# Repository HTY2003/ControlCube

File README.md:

# ControlCube
A cube of keyboard switches.
It was very bad.
It's taken apart now.
But this is a log :D

This repo includes:
* Rhino3D Design Files for the case and keycaps
* STL exports of the design files for easy viewing
* EAGLE design files for the controller board, switchplate, and switchboard
* Gerber exports of the design files for easy viewing

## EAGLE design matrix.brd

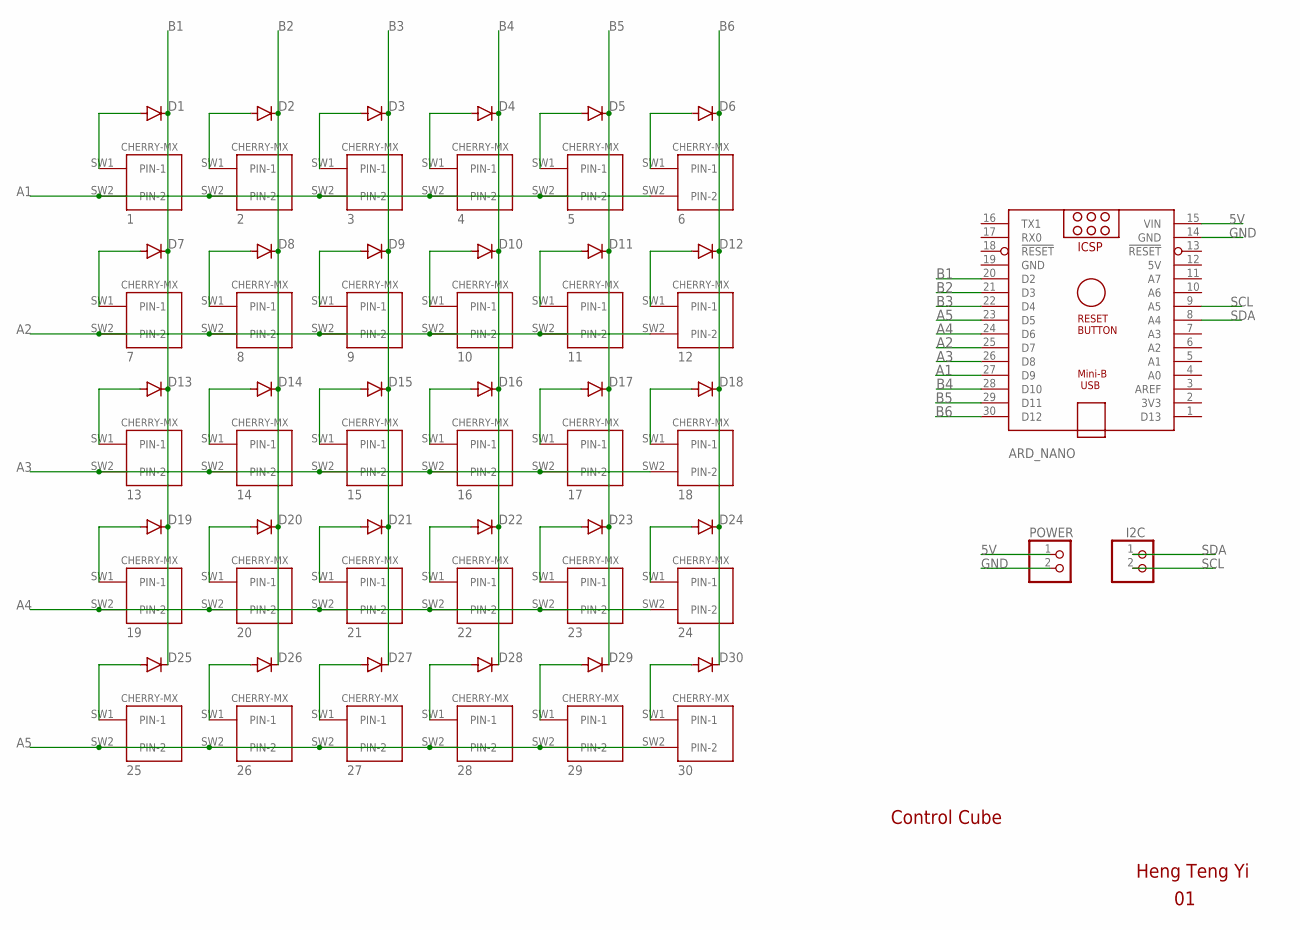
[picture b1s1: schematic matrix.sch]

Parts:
1, 2, 3, 4, 5, 6, 7, 8, 9, 10, 11, 12, 13, 14, 15, 16, 17, 18, 19, 20, 21, 22, 23, 24, 25, 26, 27, 28, 29, 30: CHERRY-MX
ARD_NANO: ARDUINO_NANO
D1, D2, D3, D4, D5, D6, D7, D8, D9, D10, D11, D12, D13, D14, D15, D16, D17, D18, D19, D20, D21, D22, D23, D24, D25, D26, D27, D28, D29, D30: 1N4148DO35-7; DO35-7
I2C: PINHD-1X2/90; 1X02/90
POWER: PINHD-1X2/90; 1X02/90

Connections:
5V: ARD_NANO.12 (5V), ARD_NANO.15 (VIN), POWER.1
A1: 1.SW2 (PIN-2), 2.SW2 (PIN-2), 3.SW2 (PIN-2), 4.SW2 (PIN-2), 5.SW2 (PIN-2), 6.SW2 (PIN-2), ARD_NANO.27 (D9)
A2: 7.SW2 (PIN-2), 8.SW2 (PIN-2), 9.SW2 (PIN-2), 10.SW2 (PIN-2), 11.SW2 (PIN-2), 12.SW2 (PIN-2), ARD_NANO.25 (D7)
A3: 13.SW2 (PIN-2), 14.SW2 (PIN-2), 15.SW2 (PIN-2), 16.SW2 (PIN-2), 17.SW2 (PIN-2), 18.SW2 (PIN-2), ARD_NANO.26 (D8)
A4: 19.SW2 (PIN-2), 20.SW2 (PIN-2), 21.SW2 (PIN-2), 22.SW2 (PIN-2), 23.SW2 (PIN-2), 24.SW2 (PIN-2), ARD_NANO.24 (D6)
A5: 25.SW2 (PIN-2), 26.SW2 (PIN-2), 27.SW2 (PIN-2), 28.SW2 (PIN-2), 29.SW2 (PIN-2), 30.SW2 (PIN-2), ARD_NANO.23 (D5)
B1: ARD_NANO.20 (D2), D1.C, D7.C, D13.C, D19.C, D25.C
B2: ARD_NANO.21 (D3), D2.C, D8.C, D14.C, D20.C, D26.C
B3: ARD_NANO.22 (D4), D3.C, D9.C, D15.C, D21.C, D27.C
B4: ARD_NANO.28 (D10), D4.C, D10.C, D16.C, D22.C, D28.C
B5: ARD_NANO.29 (D11), D5.C, D11.C, D17.C, D23.C, D29.C
B6: ARD_NANO.30 (D12), D6.C, D12.C, D18.C, D24.C, D30.C
GND: ARD_NANO.14 (GND), ARD_NANO.19 (GND), POWER.2
unnamed: 1.SW1 (PIN-1), D1.A
unnamed: 2.SW1 (PIN-1), D2.A
unnamed: 3.SW1 (PIN-1), D3.A
unnamed: 4.SW1 (PIN-1), D4.A
unnamed: 5.SW1 (PIN-1), D5.A
unnamed: 6.SW1 (PIN-1), D6.A
unnamed: 7.SW1 (PIN-1), D7.A
unnamed: 8.SW1 (PIN-1), D8.A
unnamed: 9.SW1 (PIN-1), D9.A
unnamed: 10.SW1 (PIN-1), D10.A
unnamed: 11.SW1 (PIN-1), D11.A
unnamed: 12.SW1 (PIN-1), D12.A
unnamed: 13.SW1 (PIN-1), D13.A
unnamed: 14.SW1 (PIN-1), D14.A
unnamed: 15.SW1 (PIN-1), D15.A
unnamed: 16.SW1 (PIN-1), D16.A
unnamed: 17.SW1 (PIN-1), D17.A
unnamed: 18.SW1 (PIN-1), D18.A
unnamed: 19.SW1 (PIN-1), D19.A
unnamed: 20.SW1 (PIN-1), D20.A
unnamed: 21.SW1 (PIN-1), D21.A
unnamed: 22.SW1 (PIN-1), D22.A
unnamed: 23.SW1 (PIN-1), D23.A
unnamed: 24.SW1 (PIN-1), D24.A
unnamed: 30.SW1 (PIN-1), D30.A
unnamed: 29.SW1 (PIN-1), D29.A
unnamed: 28.SW1 (PIN-1), D28.A
unnamed: 27.SW1 (PIN-1), D27.A
unnamed: 25.SW1 (PIN-1), D25.A
unnamed: 26.SW1 (PIN-1), D26.A
SCL: ARD_NANO.9 (A5), I2C.2
SDA: ARD_NANO.8 (A4), I2C.1

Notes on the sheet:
Heng Teng Yi
Control Cube

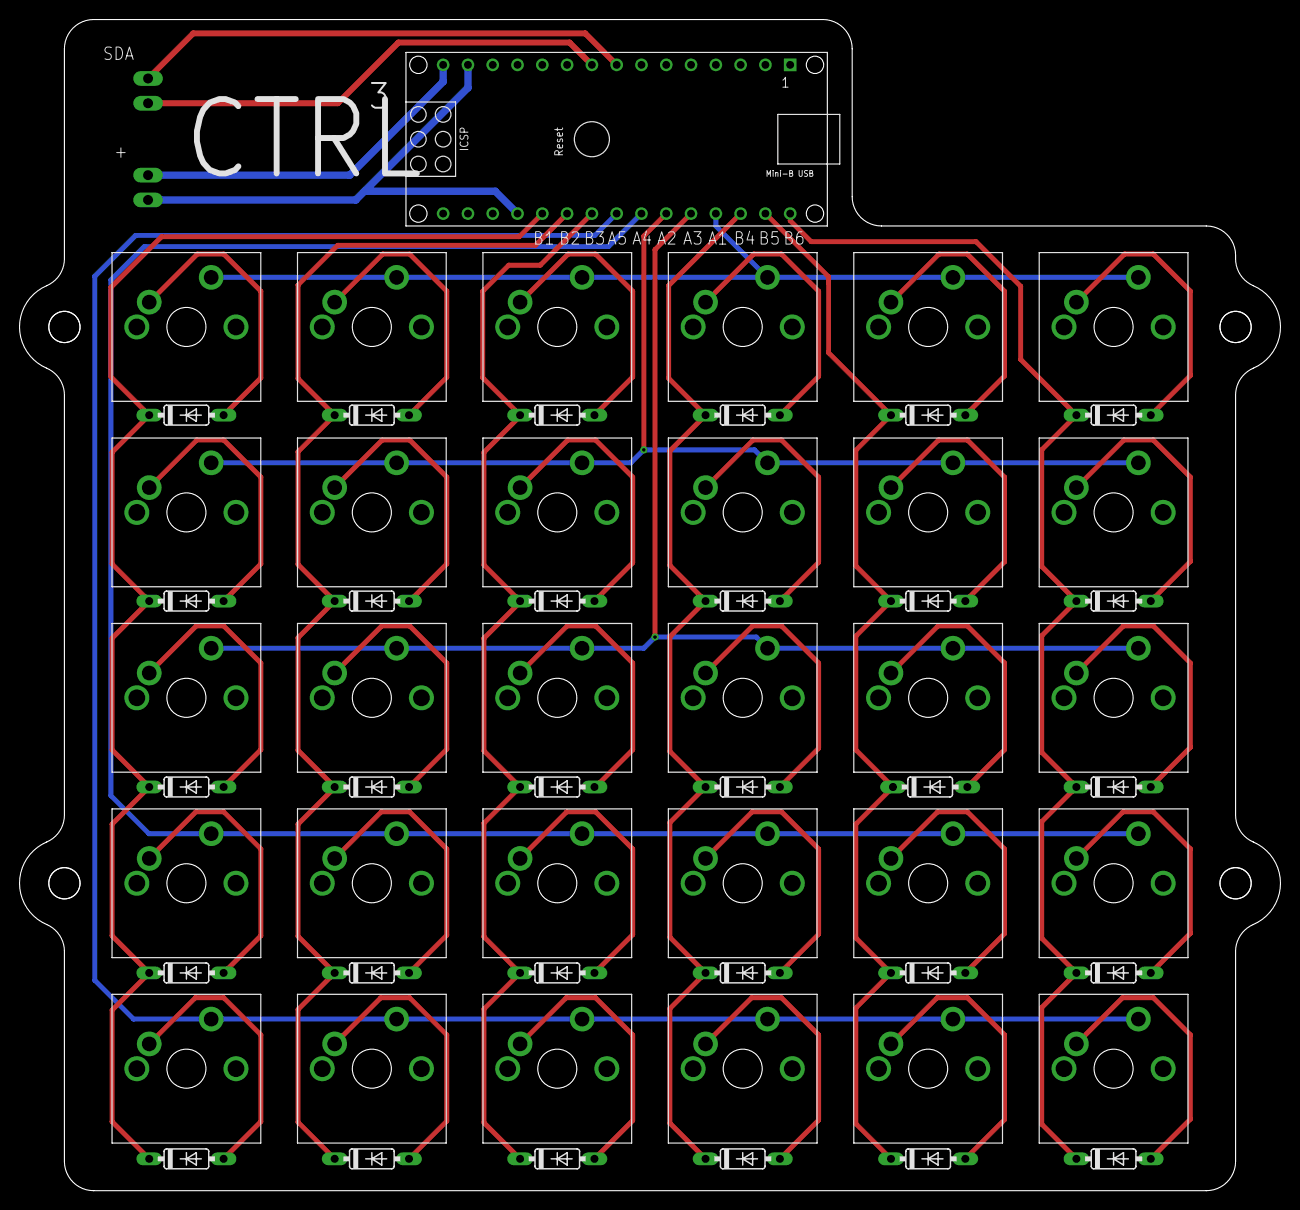
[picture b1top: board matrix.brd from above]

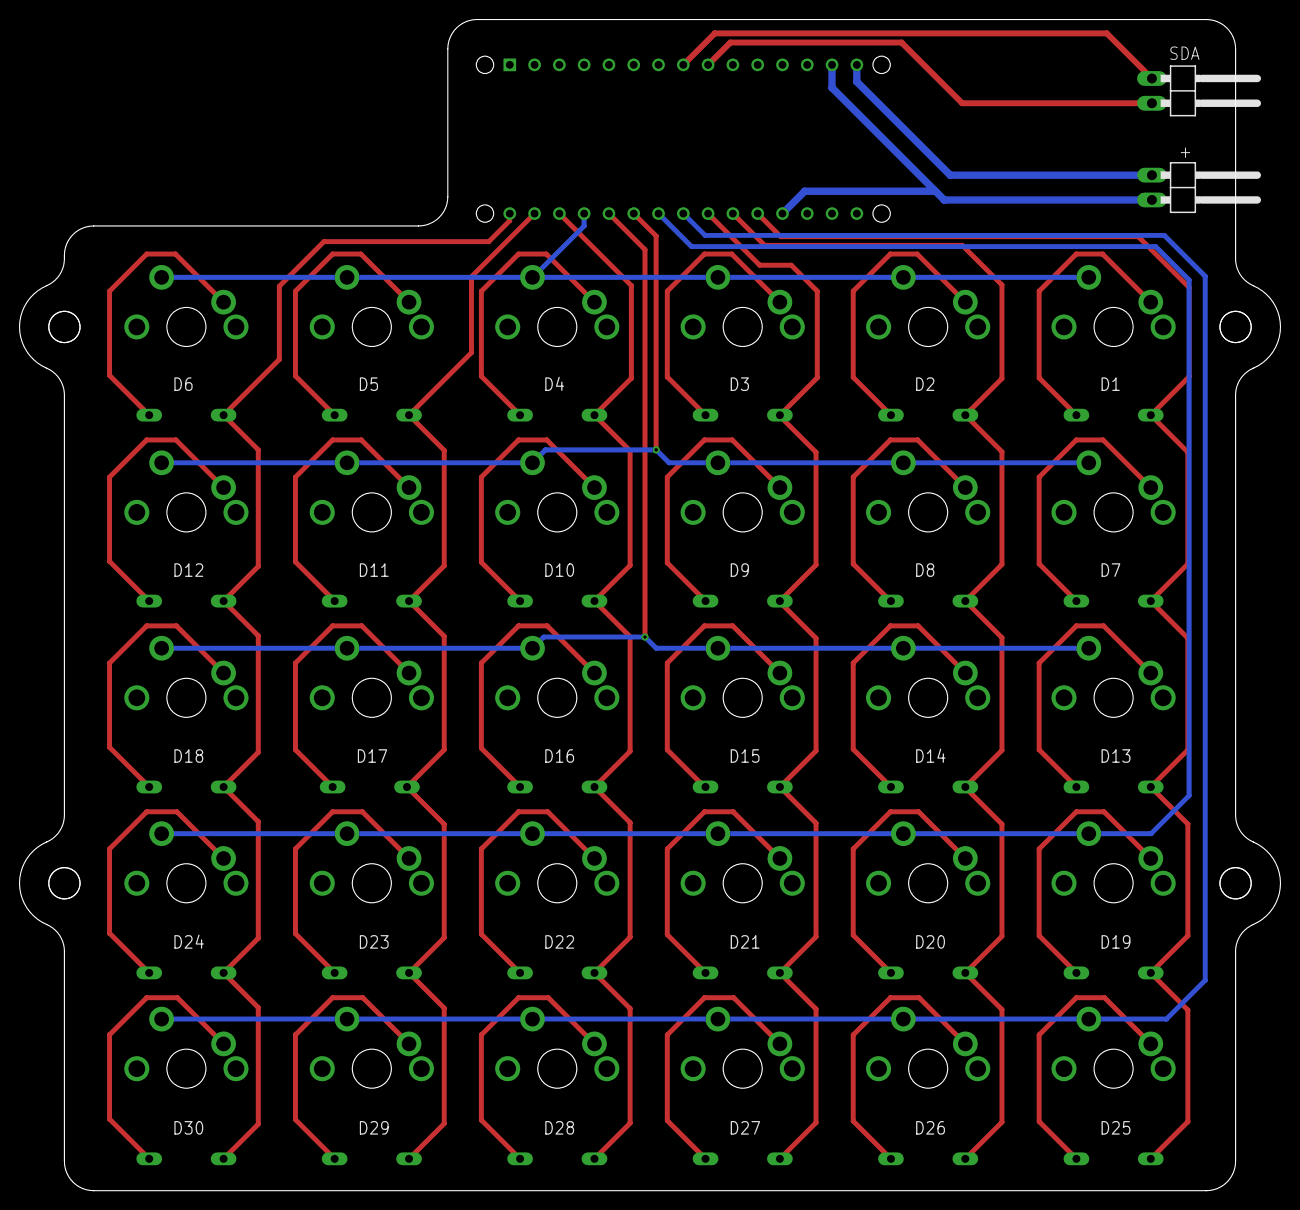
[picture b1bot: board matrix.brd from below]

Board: 2 copper layers, 129.2 x 120.0 mm, 63 parts (2 on the bottom side), 45 nets.

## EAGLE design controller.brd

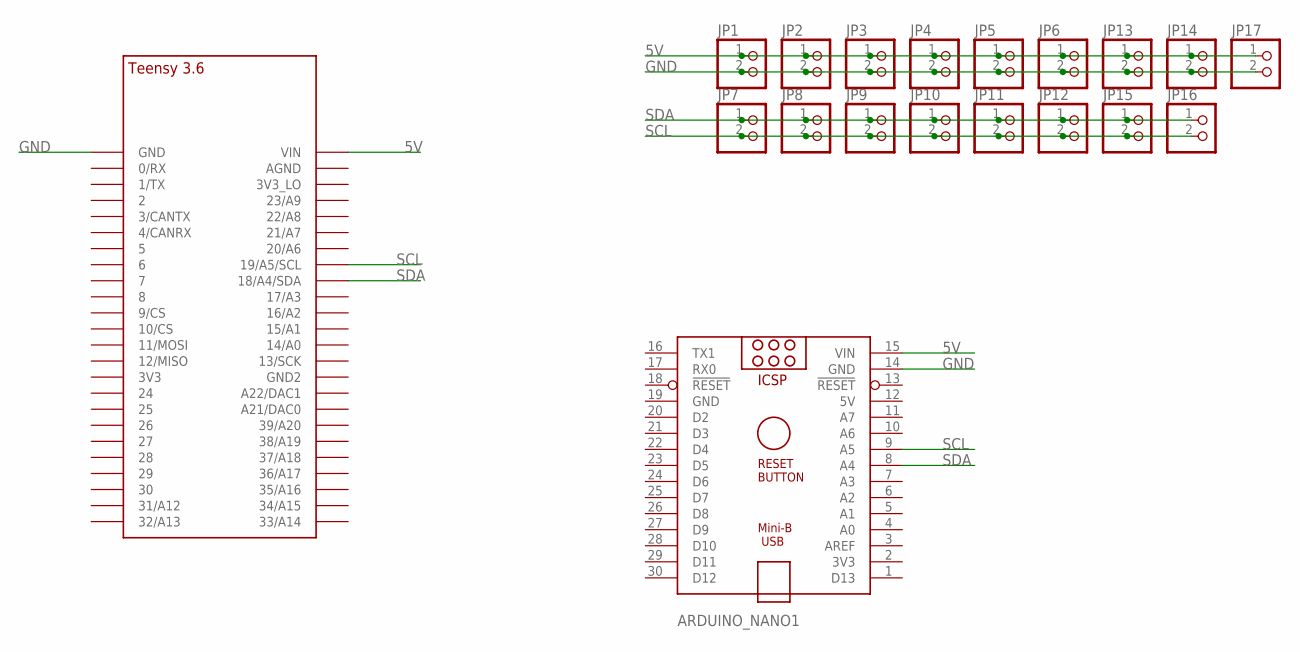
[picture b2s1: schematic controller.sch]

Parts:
ARDUINO_NANO1: ARDUINO_NANO
JP1, JP2, JP3, JP4, JP5, JP6, JP7, JP8, JP9, JP10, JP11, JP12, JP13, JP14, JP15, JP16, JP17: PINHD-1X2; 1X02
U$1: TEENSY_3.5/3.6_BASIC

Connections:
5V: ARDUINO_NANO1.12 (5V), ARDUINO_NANO1.15 (VIN), JP1.1, JP2.1, JP3.1, JP4.1, JP5.1, JP6.1, JP13.1, JP14.1, JP17.1, U$1.VIN
GND: ARDUINO_NANO1.14 (GND), ARDUINO_NANO1.19 (GND), JP1.2, JP2.2, JP3.2, JP4.2, JP5.2, JP6.2, JP13.2, JP14.2, JP17.2, U$1.GND
SCL: ARDUINO_NANO1.9 (A5), JP7.2, JP8.2, JP9.2, JP10.2, JP11.2, JP12.2, JP15.2, JP16.2, U$1.19/A5/SCL
SDA: ARDUINO_NANO1.8 (A4), JP7.1, JP8.1, JP9.1, JP10.1, JP11.1, JP12.1, JP15.1, JP16.1, U$1.18/A4/SDA

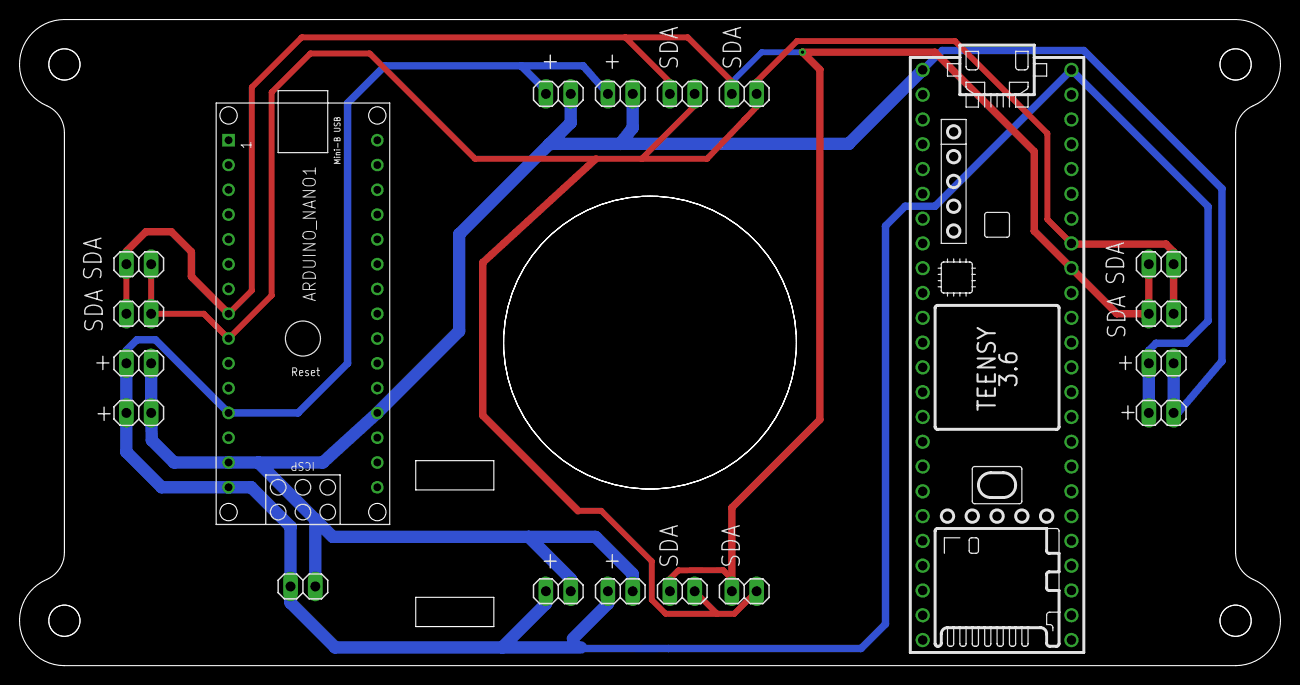
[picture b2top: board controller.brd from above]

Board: 2 copper layers, 129.2 x 66.2 mm, 19 parts (0 on the bottom side), 4 nets.

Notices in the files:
parts and their libraries:
SparkFun-Aesthetics: Licensing: Creative Commons ShareAlike 4.0 International - https://creativecommons.org/licenses/by-sa/4.0
